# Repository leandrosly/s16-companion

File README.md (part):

# S16 Companion

Display de pulso e "ponte" Bluetooth para o monociclo elétrico **KingSong KS-S16**, feito com um ESP32-S3 com tela touch de 2,8".

O display se conecta na roda, mostra os dados em tempo real, grava logs, controla farol, buzina, LEDs e música, e repassa tudo para os apps do celular (EUC World, Mono Riders, KingSong) como se ele fosse a própria roda.

> Este README é também o **caderno do projeto**: o que já funciona, o que estamos fazendo agora, as ideias guardadas para depois e tudo o que já descobrimos sobre os protocolos.

---

## Sumário

1. [Foco atual](#1-foco-atual)
2. [Estado do projeto](#2-estado-do-projeto)
3. [Hardware](#3-hardware)
4. [Como compilar](#4-como-compilar)
5. [Estrutura do repositório](#5-estrutura-do-repositório)
6. [Usando o display](#6-usando-o-display)
7. [Arquitetura da ponte BLE](#7-arquitetura-da-ponte-ble)
8. [Protocolo KingSong (S16)](#8-protocolo-kingsong-s16)
9. [Protocolo do módulo de LEDs "Dream" (Happy Lighting)](#9-protocolo-do-módulo-de-leds-dream-happy-lighting)
10. [Lições aprendidas (as pegadinhas)](#10-lições-aprendidas-as-pegadinhas)
11. [Roadmap](#11-roadmap)
12. [Ideias guardadas](#12-ideias-guardadas)
13. [Ferramentas e técnicas de investigação](#13-ferramentas-e-técnicas-de-investigação)
14. [Referências](#14-referências)

---

## 1. Foco atual

Para não misturar tudo: **no máximo 3 frentes ativas**. O resto fica na [lista de ideias](#12-ideias-guardadas) até uma destas terminar.

| # | Frente | Próximo passo concreto |
|---|---|---|
| 1 | **Pareamento do S16 Controle (PAREAMENTO_V2)** | ✅ Funcionou em 15/10 (reinício, sono e bateria desconectada: o controle volta sozinho). Confirmar no uso do dia a dia: depois de >15 min (o celular troca o endereço "no ar"), com os apps juntos e numa volta de verdade. Se seguir firme, passa para "Funcionando". |
| 2 | **Luz de freio** | ✅ Feita (14/10) — **testar andando**: ver se os limites (−2 A acende, −0,8 A apaga) ficam bons na prática (descida longa também regenera e acende). Ver [Luz de freio](#luz-de-freio). |
| 3 | **Alcance do 433 na luva** | Na volta de 16/10 o controle e os piscas "funcionam no geral" mas falham na rua. Suspeita: antenas molinha (~20 mm) escondidas atrás do display, as 3 plaquinhas (RX, TX, MPU) emboladas. Testar antena de fio esticado (**17,3 cm** = ¼ de onda), afastar RX/TX entre si e do display, e ver se o 5 V do conector existe na bateria (o STX882 transmite mais forte em 5 V). Ver [433 na prática](#433-na-prática-antenas). |

**Bateria do display** (saiu do foco): 18650 de ~3000 mAh aguentou **3,5 h de volta e voltou com ~60%** (16/10) → consumo na casa de ~300–350 mA, autonomia estimada de 8 h+. O % vem da tensão, então é aproximado. Falta: conferir a leitura com o multímetro e a célula fina definitiva.

**Concluídos** (na ponte v5 MIDIA): ✅ MPU (tela pelo pulso + config na tela), ✅ som (piezo), ✅ piscas 433 MHz, ✅ mochila Dream (tela, conectar, estado salvo), ✅ cortina de Ajustes, ✅ print da tela, ✅ barra de ícones com bateria e "carregando", ✅ pico do PWM, ✅ controle da buzina como botões do display (receptor no IO3) + buzina externa pareada com o display, ✅ dormir/acordar (sozinho, botão, acorda mexendo), ✅ indicadores das lanternas na principal, ✅ luz de freio, ✅ pareamento do S16 Controle que sobrevive ao reinício (V2, em observação).

**Lembrete de pedal:** desativar a **economia de bateria do celular** antes de rodar — com ela ligada o GPS do EUC World ficou falhando na metade da volta de 11/10.

---

## 2. Estado do projeto

### Funcionando ✅

**Ponte BLE**
- O display conecta na roda e se apresenta aos celulares com o mesmo nome e os mesmos serviços (clone completo da GATT).
- **EUC World, Mono Riders, WheelLog e app da KingSong** funcionando pela ponte, com **2 apps garantidos** (já rodaram os 4 juntos na v5 2APPS, com o Android dividindo conexões).
- **WheelLog só funciona na v5 2APPS:** ele exige a lista de serviços idêntica à da roda, e a v5 MIDIA tem 2 serviços a mais (HID `1812` e bateria `180F`).
- **Controle de mídia** (v5 MIDIA): música e volume do celular direto pelo display, numa identidade Bluetooth separada ("S16 Controle"). **Desde 15/10 (PAREAMENTO_V2) o pareamento sobrevive** a reinício, sono e falta de bateria: o controle volta sozinho. Ver [Controle de mídia](#controle-de-mídia-v5-midia).
- **Coexistência provada** com `MAX_CONNECTIONS` 6: roda + apps + controle de mídia + cliente da mochila (Dream) + MPU + som + 433, ninguém caiu.
- Relógio acertado pela própria roda ao conectar.

**Tela e controles**
- 3 páginas por deslize (**BMS** ← **principal** → **controles**) + **cortina de Ajustes** (de cima) + **cortina dos Piscas** (de baixo). Ver [Telas](#telas-deslizar-o-dedo).
- Velocidade com cor pelo PWM, barra de PWM com **pico** (segura 5 s), indicadores das lanternas dos lados da velocidade.
- Barra de cima só com ícones: roda, apps, controle de mídia, buzina, mochila, ventoinha, gravação, bateria do display (com raio de "carregando") e hora.
- Buzina no botão BOOT e na tela; farol (liga/desliga/auto), LEDs, volume da roda.
- **Print da tela** em BMP no cartão (`/prints`).

**Periféricos**
- **MPU-6050:** a tela acende/apaga pela posição do pulso (`Tela auto` na cortina, começa desligado). Config na tela: GRAVAR a posição de olhar, ângulos de acender/apagar, PADRÃO. Também acorda o display do sono, se `Acorda mexendo` estiver ligado.
- **Som:** codec ES8311 + I2S numa tarefa separada, piezo a 4 kHz (ressonância do piezo de 35 mm). Bipes de confirmação e alarme de bateria baixa. `Som` na cortina liga/desliga.
- **Piscas / lanternas 433 MHz** (STX882 no IO21, RMT): modo base (apagado/laranja/vermelho/piscando, salvo) e piscas esq/dir na cortina de baixo; apertar o pisca de novo volta ao modo base.
- **Controle da buzina como botões do display** (receptor SRX882S no IO3): buzina da roda, piscas esq/dir, buzina externa e desligar o alarme dela. Ver [Controle da buzina](#controle-da-buzina-sem-fio-43392-mhz).
- **Buzina externa** pareada com a identidade do display (`00 9F 1D`): tela com as 7 funções do controle original.
- **Mochila (Dream) como 2º cliente BLE:** conecta sozinha depois da roda (conexão bloqueante de até 2,5 s, **só com a roda parada** — a tentativa trava o loop, e andando isso pararia freio, buzina e 433; se não acha, tenta de novo em 15 s nas 3 primeiras vezes, depois a cada 1 min e depois a cada 5 min; o botão CONECTAR / `dream on` zera e tenta na hora), tela própria (liga, cores, brilho, efeito, DEMO, velocidade), estado salvo na flash e reaplicado ao reconectar.
- **Luz de freio** automática pela corrente negativa: lanternas vermelhas + mochila vermelha no máximo. Ver [Luz de freio](#luz-de-freio).

**Energia**
- Leitura da bateria no IO9, % e "carregando" (USB do PC ou degrau de tensão). Alarme abaixo de 3,35 V.
- **Dorme sozinho** (10 min sem roda e sem USB, ou bateria < 3,30 V), botão **Dormir** na cortina, acorda no BOOT (ou mexendo). Ao acordar, lanternas e mochila voltam como estavam.

**Registros e configuração**
- Logs no cartão SD: eventos sempre, viagem sob demanda (5 linhas/s).
- Configuração pelo Serial e pela tela, salva na flash. Versão do firmware no Serial e no rodapé da cortina.

### Em andamento 🔧

- Protocolo do módulo de LEDs Dream: comandos e resposta de estado decifrados; o índice do efeito não aparece na resposta e os quadros `D0`/`A0` seguem sem significado (baixa prioridade).
- PAREAMENTO_V2 em observação (ver [Foco atual](#1-foco-atual)).

### Problemas conhecidos ⚠️

- **Um 3º app** às vezes funciona porque o Android coloca dois apps na mesma conexão, mas pode cair em cascata. Garantido: 2 apps.
- **Disputa entre núcleos no `maps`** (revisão de 17/10, item 6, pendente): o `onDisconnect` da roda zera os ponteiros remotos no núcleo do Bluetooth enquanto o `loop()` (`syncSubscriptions`/`processWrites`) testa e usa o mesmo ponteiro; e o `mapGatt()` limpa o `maps` enquanto callbacks do celular o percorrem. Raro (nunca visto na prática), mas pode reiniciar a placa. Conserto: mutex ou copiar o ponteiro para uma variável local antes de testar e usar. Fazer separado e com teste.
- **Limite de 3 pareamentos** guardados (`CONFIG_BT_NIMBLE_MAX_BONDS` padrão da NimBLE). Com um celular só não faz diferença; com mais aparelhos, aumentar no `nimconfig.h`.
- Os comandos de próxima/anterior **da roda** (`95`) pulam mais de uma música (é da roda, acontece também no app da KingSong). A v5 MIDIA resolve controlando o celular direto.
- O app da KingSong mostra o histórico com horário deslocado (bug de fuso do app; a roda guarda a hora local certa).

---

## 3. Hardware

### Placa principal: ES3C28P (LCDWIKI)

ESP32-S3 (16 MB flash, 8 MB PSRAM OPI), tela IPS 2,8" 240×320 (ILI9341V, SPI), touch capacitivo FT6336G (I2C 0x38), slot microSD (SDIO), amplificador de áudio 1,5 W, LED RGB, carregador de LiPo.

| Função | Pinos |
|---|---|
| Tela (SPI) | SCK 12, MOSI 11, MISO 13, CS 10, DC 46, backlight 45 |
| Touch (I2C) | SDA 16, SCL 15, INT 17, RST 18 — **touch girado 180°: inverter X e Y** |
| Cartão SD (SDIO, 1 linha) | CLK 38, CMD 40, D0 39 |
| Áudio (I2S) | EN 1 (amplificador: 0 = liga), MCLK 4, BCLK 5, LRCK 7, **IO8 = som ESP32→codec**, IO6 = microfone codec→ESP32. Codec ES8311 configurado por I2C (0x18) |
| Bateria (ADC) | 9 — lê **metade** da tensão (divisor 2:1 da placa); o firmware multiplica por 2 |
| LED RGB (WS2812) | 42 |
| Botão BOOT | 0 (usado como buzina) |
| USB nativo | 19, 20 |

**Conectores (todos 1,25 mm):**

| Conector | Pinos | Plano de uso |
|---|---|---|
| I2C | 3.3V, GND, IO15 (SCL), IO16 (SDA) | **MPU-6050 (0x68)** no mesmo barramento do touch (0x38) e do codec ES8311 (0x18), usando as funções `lgfx::i2c` da LovyanGFX (testado: 0 erros com o touch em uso) |
| GPIO | IO21, IO14, IO3, IO2 | IO21 = STX882 (transmissor 433 MHz); IO14 = INT do MPU (acorda o display do sono com `Acorda mexendo`); **IO3 = DATA do receptor SRX882S** (controle 433); IO2 = livre (era botão do pisca; os botões físicos foram desligados com `BOTOES_PISCA = false`) |
| UART | 5V, GND, TXD (IO44), RXD (IO43) | livre (ex.: UART para GPS) |
| BAT | + / − | LiPo 3,7 V (**conferir a polaridade antes de ligar!**). Carregador **TP4054** na placa (até 500 mA): carrega sozinho com o USB-C ligado, nada a fazer no firmware. Com USB presente a placa roda pelo USB (Q3 corta a bateria). ⚠️ **A placa não tem proteção de descarga**: usar célula **com placa de proteção (PCM)** — 18650 "protegida" ou LiPo "with protection board". |
| SPEAKER | 2 pinos | piezo passivo + 100 Ω em série (saída em ponte: nenhum dos pinos é GND) |
| BOOT (IO0) | soldar nos pads do botão | botão da buzina em paralelo (não segurar ao ligar a placa) |

**Receptor SRX882S no display:** VCC → 3V3 · GND → GND · **CS → 3V3** (obrigatório: solto = dormindo) · DATA → IO3 · antena espiral. Alimentado em **3,3 V** (não 5 V), para a saída DATA não mandar 5 V no ESP32.

Não há outros pinos livres no chip. Para mais portas: **MCP23017** (16 GPIO por I2C).

### Outros

- **2× ESP32-C3 Supermini**: protótipos (ponte v3 com LCD 16×2, captura de 433 MHz) e, no futuro, controlador da fita de LED da mochila.
- **Módulo de LEDs iFlight "Dream#0E4D"**: mochila dos drones, controlado pelo app Happy Lighting — e agora pelo display.
- **Rádio 433 MHz**: **STX882** (transmissor, no display, IO21) + **SRX882S** (receptor, no display, IO3). FS1000A + MX-RM-5V na gaveta.
- **MPU-6050** (GY-521), no I2C do display, INT no IO14.
- **Lanternas/piscas tipo bike** (par no capacete + par na traseira do mono), controle sem fio 433,92 MHz.
- **Buzina sem fio 433 MHz** com controle de 5 botões (o controle virou entrada do display; a buzina obedece à identidade do display).
- Bateria de teste: 18650 protegida (definitiva: LiPo fina `404070` com proteção).

---

## 4. Como compilar

**Versão do arquivo:** a 1ª linha do `.ino` traz `// VERSAO: v5-AAAAMMDDHHMM` (data e hora em que foi gerado). A mesma versão aparece no Serial ao ligar (`=== S16 Companion ponte v5-... ===`) e no rodapé da cortina de Ajustes — assim dá pra saber qual arquivo está gravado no display.

### Arduino IDE

- Core **esp32 by Espressif 3.3.12**.
- Bibliotecas:
  - **NimBLE-Arduino 2.5.1** — **COM O PATCH** da pasta `patch_nimble_2.5.1/` (ver o README de lá). Sem o patch: o EUC World recusa a ponte, a placa reinicia ao desconectar apps e os anúncios são recusados. O `nimconfig.h` do patch também liga a **privacidade no host** (`CONFIG_BT_NIMBLE_HOST_BASED_PRIVACY 1`), exigida pelo `PAREAMENTO_V2` — sem ela a compilação para num `#error` que explica.
  - **LovyanGFX** (lovyan03).
  - `SD_MMC` e `Preferences` já vêm com o core.

> ⚠️ **Não atualize a NimBLE-Arduino** sem refazer o patch. Ao trocar de PC: instale a 2.5.1 e copie os 5 arquivos do patch. Mudar o `nimconfig.h` faz a biblioteca inteira recompilar (a 1ª compilação demora mais).

**Chaves no topo do sketch:** `USAR_SOM` (0 desliga todo o som, para isolar problemas) e `PAREAMENTO_V2` (1 = pareamento novo do S16 Controle; 0 = jeito antigo, que repareia a cada reinício).

### Menu Ferramentas (ES3C28P)

```
Placa:            ESP32S3 Dev Module
USB CDC On Boot:  Enabled
USB Mode:         Hardware CDC and JTAG
Flash Size:       16MB (128Mb)       ← antes do Partition Scheme
Partition Scheme: 16M Flash (3MB APP/9.9MB FATFS)
PSRAM:            OPI PSRAM          ← obrigatório
JTAG Adapter:     Disabled
```

Conferências: no fim da gravação, "Maximum is 3145728 bytes"; no Serial, `PSRAM: 8388608 bytes`.

### Decodificar um reinício (Guru Meditation)

1. Com o binário que está na placa: **Sketch > Export Compiled Binary** (gera o `.elf` em `build/`).
2. Copie a linha `Backtrace:` e rode:

```powershell
& "$env:LOCALAPPDATA\Arduino15\packages\esp32\tools\esp-x32\2601\bin\xtensa-esp32s3-elf-addr2line.exe" -pfiaC -e "CAMINHO\sketch.ino.elf" 0x4200... 0x4200...
```

Os endereços só valem para **o mesmo binário**. Alternativa: extensão "ESP Exception Decoder" (dankeboy36).

---

## 5. Estrutura do repositório

| Pasta / arquivo | O que é |
|---|---|
| `ks_s16_ponte_v5_midia/` | **Versão principal**: ponte + 2 apps + controle de mídia (2 identidades BLE) |
| `ks_s16_ponte_v5_2apps/` | Mesma ponte, sem controle de mídia (mais simples, fallback estável; **a única que funciona com o WheelLog**) |
| `patch_nimble_2.5.1/` | Os 5 arquivos corrigidos da NimBLE e onde vai cada um |
| `ks_s16_ponte_v4_s3/` | v4: primeira versão no ES3C28P (3 telas, buzina no BOOT, logs, mídia HID). Histórico |
| `ks_s16_ponte/` | v3: ponte com clone completo da GATT no ESP32-C3 + LCD 16×2. Histórico |
| `ks_s16_lcd_test/` | Primeiro teste: roda → ESP32-C3 → LCD 16×2. Histórico |
| `galeria_fotos/` | Exemplo de aprendizado: tela + touch + sprites + zoom (+ script `converter_fotos.py`) |
| `captura_433/` | Sketch para descobrir os códigos do controle dos piscas (ESP32-C3) |
| `ponte_c3/` | **Ponte no ESP32-C3 fixo na roda** (plano "C3 na roda", etapa 1: só a ponte BLE) |
| `app_android/` | **App Android** (Kotlin + Jetpack Compose, BLE nativo): conecta no C3 pelo canal da FFE1 (HELLO arg 1 = "sou o app") e controla piscas, lanternas, freio, fitas e buzina externa. Código em `app/src/main/java/` (arquivos soltos, sem as pastas do pacote). Abrir a pasta no Android Studio |
| `laboratorio_sons/` | **Laboratório de sons** (página HTML, abre no navegador): motores sintetizados que reagem à velocidade/aceleração (Harley V2, V8, scooter 2T, turbina, elétrico Tron, nave, ou um loop gravado) e buzinas (Klaxon, carro, caminhão, sci-fi). Protótipo dos sons do futuro app Android |
| `medidor_433/` | **Medidor de alcance do 433** (ESP32-C3 + SRX882S + LCD 16×2): conta quantas repetições das rajadas do `433 teste` chegam |
| `teste_i2c_mpu/` | Teste do MPU-6050 dividindo o I2C com o touch (Plano A LovyanGFX / Plano B Wire1) |
| `teste_tx433/` | Display imitando o controle dos piscas (STX882 no IO21, RMT) |
| `teste_mochila/` | Display como cliente BLE do módulo Dream: liga/cor/efeito/handshake |
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
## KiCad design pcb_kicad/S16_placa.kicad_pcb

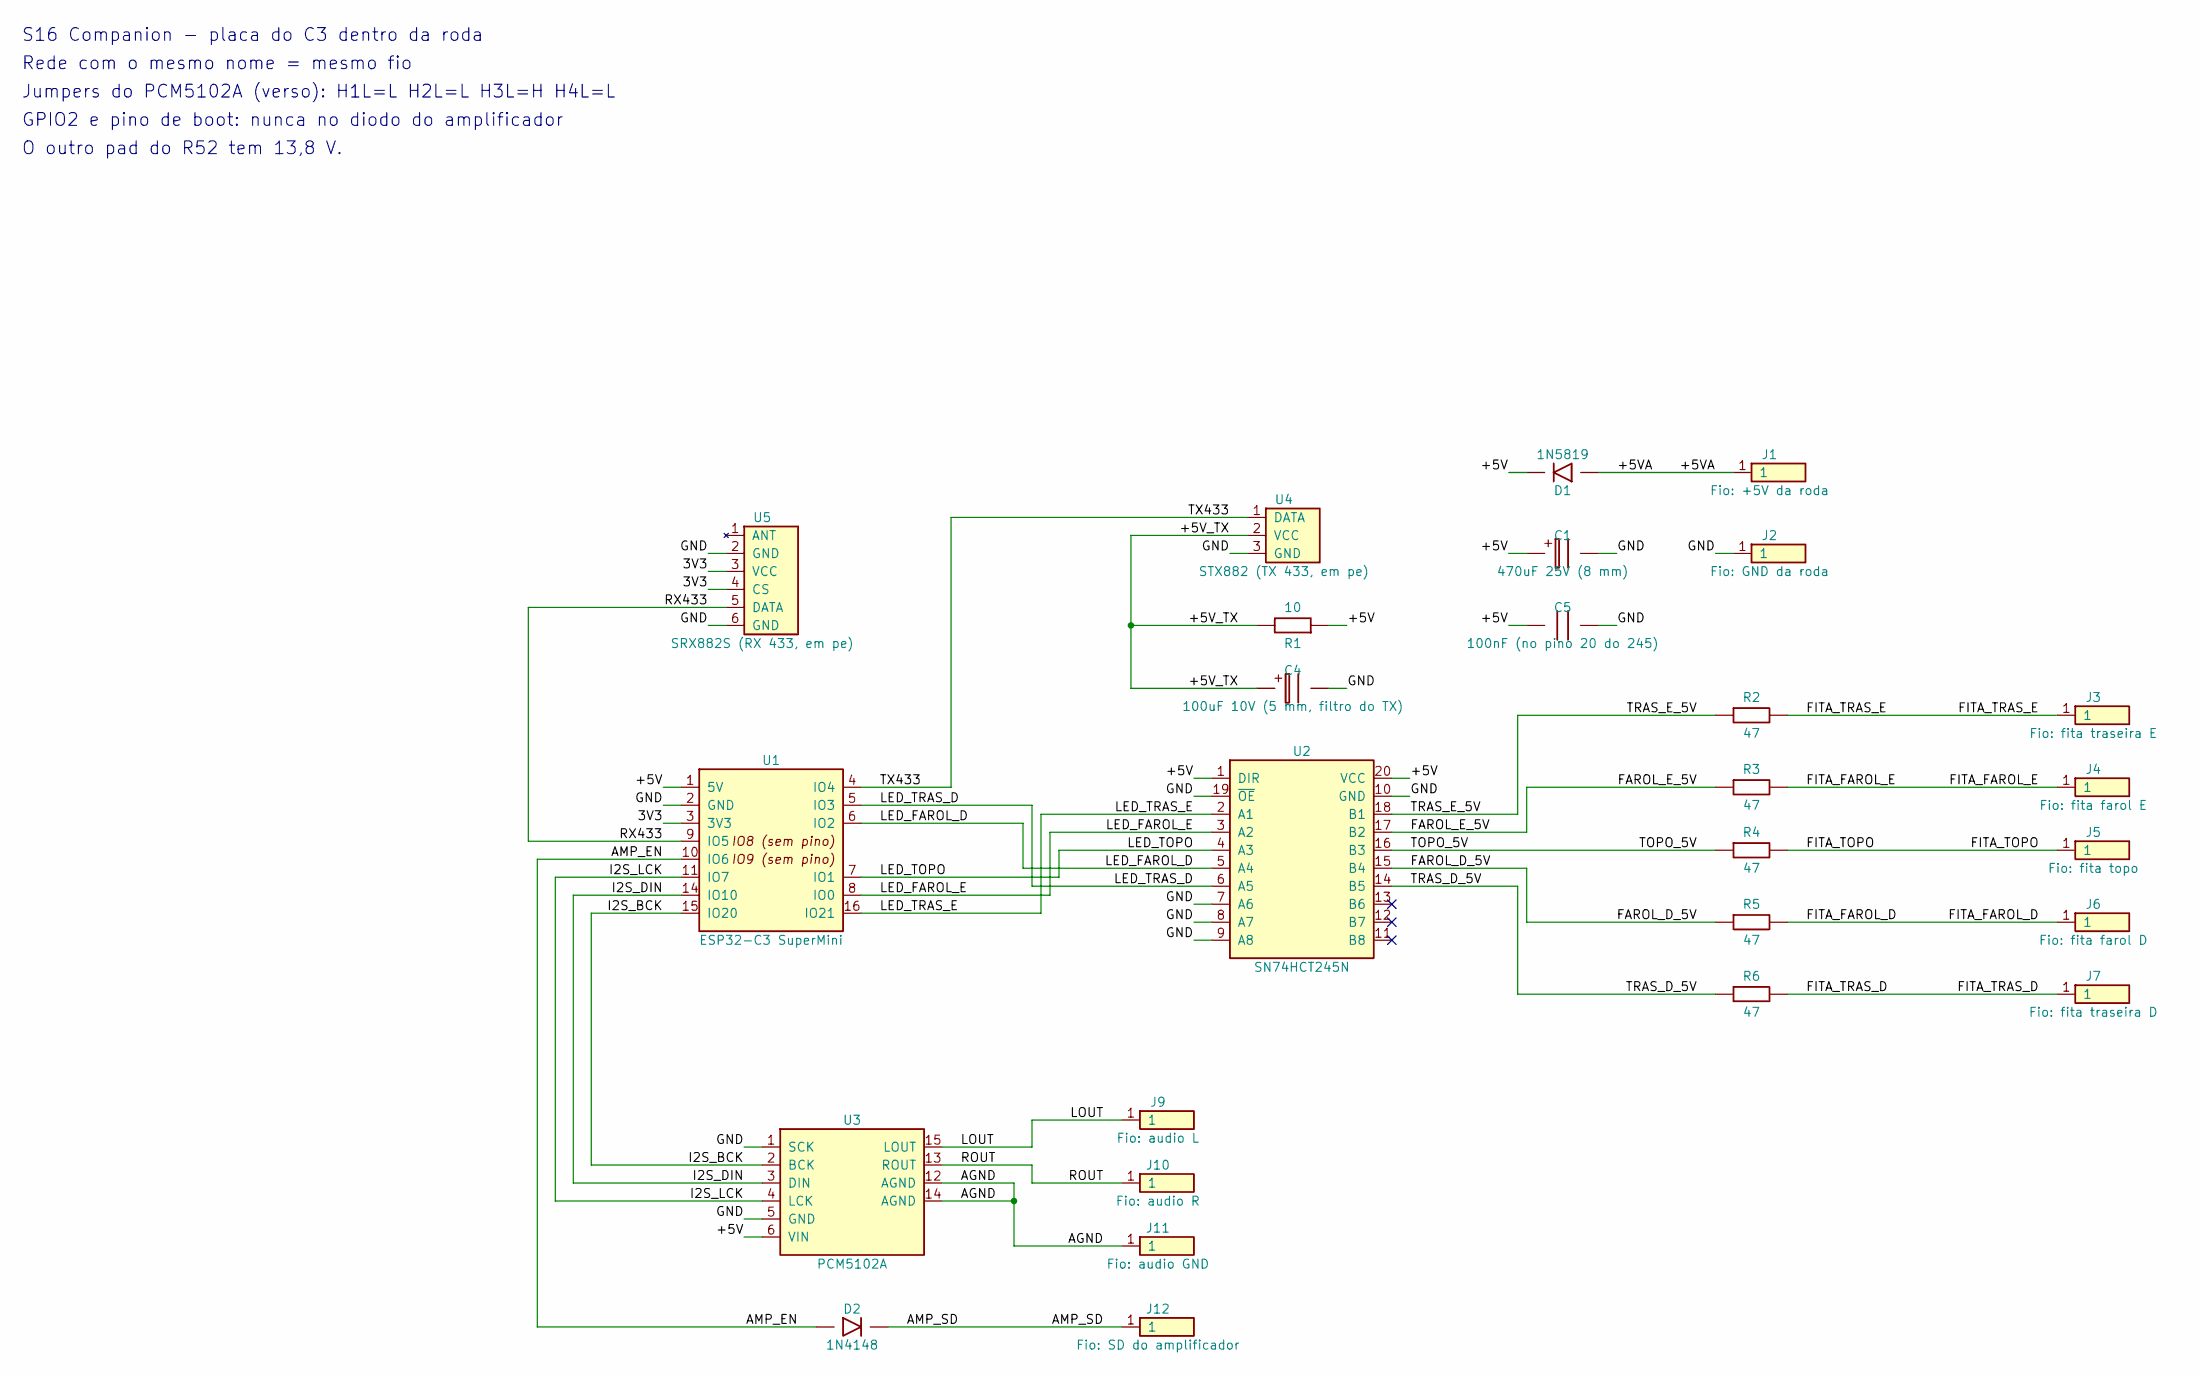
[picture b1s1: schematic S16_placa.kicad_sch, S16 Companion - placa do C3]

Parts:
C1: 470uF 25V (8 mm); CP_Radial_D8.0mm_P3.50mm
C4: 100uF 10V (5 mm, filtro do TX); CP_Radial_D5.0mm_P2.00mm
C5: 100nF (no pino 20 do 245); C_Disc_D5.0mm_W2.5mm_P5.00mm
D1: 1N5819; D_DO-41_SOD81_P7.62mm_Horizontal
D2: 1N4148; D_DO-35_SOD27_P7.62mm_Horizontal
J1: Fio: +5V da roda; TestPoint_THTPad_D2.5mm_Drill1.2mm
J2: Fio: GND da roda; TestPoint_THTPad_D2.5mm_Drill1.2mm
J3: Fio: fita traseira E; TestPoint_THTPad_D2.0mm_Drill1.0mm
J4: Fio: fita farol E; TestPoint_THTPad_D2.0mm_Drill1.0mm
J5: Fio: fita topo; TestPoint_THTPad_D2.0mm_Drill1.0mm
J6: Fio: fita farol D; TestPoint_THTPad_D2.0mm_Drill1.0mm
J7: Fio: fita traseira D; TestPoint_THTPad_D2.0mm_Drill1.0mm
J9: Fio: audio L; TestPoint_THTPad_D2.0mm_Drill1.0mm
J10: Fio: audio R; TestPoint_THTPad_D2.0mm_Drill1.0mm
J11: Fio: audio GND; TestPoint_THTPad_D2.0mm_Drill1.0mm
J12: Fio: SD do amplificador; TestPoint_THTPad_D2.0mm_Drill1.0mm
R1: 10; R_Axial_DIN0207_L6.3mm_D2.5mm_P7.62mm_Horizontal
R2, R3, R4, R5, R6: 47; R_Axial_DIN0207_L6.3mm_D2.5mm_P2.54mm_Vertical
U1: ESP32-C3 SuperMini; ESP32-C3_SuperMini
U2: SN74HCT245N; DIP-20_W7.62mm
U3: PCM5102A; PCM5102A_Modulo
U4: STX882 (TX 433, em pe); STX882_EmPe
U5: SRX882S (RX 433, em pe); SRX882S_EmPe

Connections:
/3V3: U1.3 (3V3), U5.3 (VCC), U5.4 (CS)
/+5V: C1.1, C5.1, D1.1, R1.1, U1.1 (5V), U2.1 (DIR), U2.20 (VCC), U3.6 (VIN)
/+5VA: D1.2, J1.1 (1_1)
/+5V_TX: C4.1, R1.2, U4.2 (VCC)
/AGND: J11.1 (1_1), U3.12 (AGND), U3.14 (AGND)
/AMP_EN: D2.2, U1.10 (IO6)
/AMP_SD: D2.1, J12.1 (1_1)
/FAROL_D_5V: R5.1, U2.15 (B4)
/FAROL_E_5V: R3.1, U2.17 (B2)
/FITA_FAROL_D: J6.1 (1_1), R5.2
/FITA_FAROL_E: J4.1 (1_1), R3.2
/FITA_TOPO: J5.1 (1_1), R4.2
/FITA_TRAS_D: J7.1 (1_1), R6.2
/FITA_TRAS_E: J3.1 (1_1), R2.2
/GND: C1.2, C4.2, C5.2, J2.1 (1_1), U1.2 (GND), U2.7 (A6), U2.8 (A7), U2.9 (A8), U2.10 (GND), U2.19 (~OE), U3.1 (SCK), U3.5 (GND), U4.3 (GND), U5.2 (GND), U5.6 (GND)
/I2S_BCK: U1.15 (IO20), U3.2 (BCK)
/I2S_DIN: U1.14 (IO10), U3.3 (DIN)
/I2S_LCK: U1.11 (IO7), U3.4 (LCK)
/LED_FAROL_D: U1.6 (IO2), U2.5 (A4)
/LED_FAROL_E: U1.8 (IO0), U2.3 (A2)
/LED_TOPO: U1.7 (IO1), U2.4 (A3)
/LED_TRAS_D: U1.5 (IO3), U2.6 (A5)
/LED_TRAS_E: U1.16 (IO21), U2.2 (A1)
/LOUT: J9.1 (1_1), U3.15 (LOUT)
/ROUT: J10.1 (1_1), U3.13 (ROUT)
/RX433: U1.9 (IO5), U5.5 (DATA)
/TOPO_5V: R4.1, U2.16 (B3)
/TRAS_D_5V: R6.1, U2.14 (B5)
/TRAS_E_5V: R2.1, U2.18 (B1)
/TX433: U1.4 (IO4), U4.1 (DATA)

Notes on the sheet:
Jumpers do PCM5102A (verso): H1L=L H2L=L H3L=H H4L=L
GPIO2 e pino de boot: nunca no diodo do amplificador
S16 Companion - placa do C3 dentro da roda
O outro pad do R52 tem 13,8 V.
Rede com o mesmo nome = mesmo fio

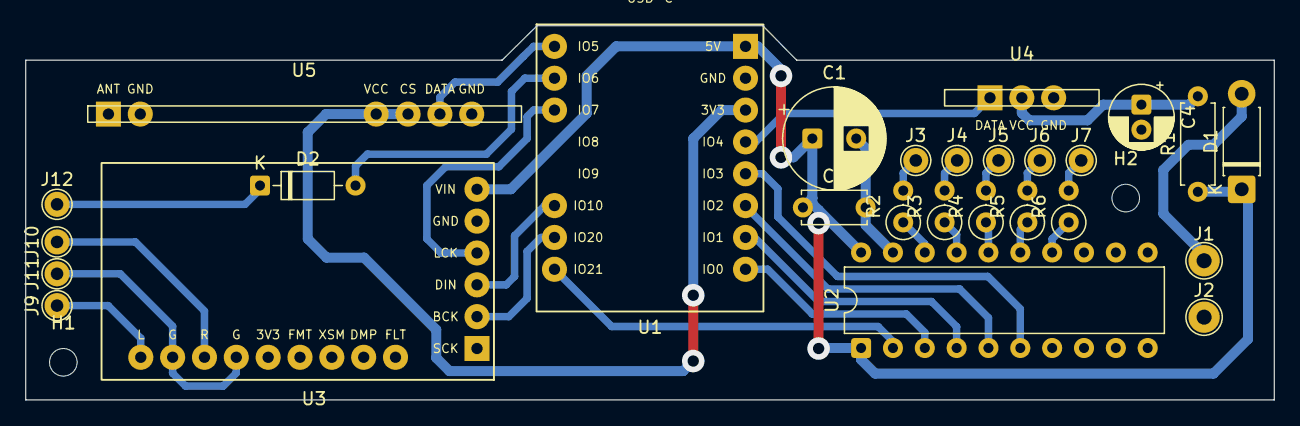
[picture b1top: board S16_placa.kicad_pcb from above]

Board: 2 copper layers, 99.6 x 29.8 mm, 29 parts (0 on the bottom side), 30 nets.

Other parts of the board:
H1, H2: Fixacao M2; MountingHole_2.2mm_M2
